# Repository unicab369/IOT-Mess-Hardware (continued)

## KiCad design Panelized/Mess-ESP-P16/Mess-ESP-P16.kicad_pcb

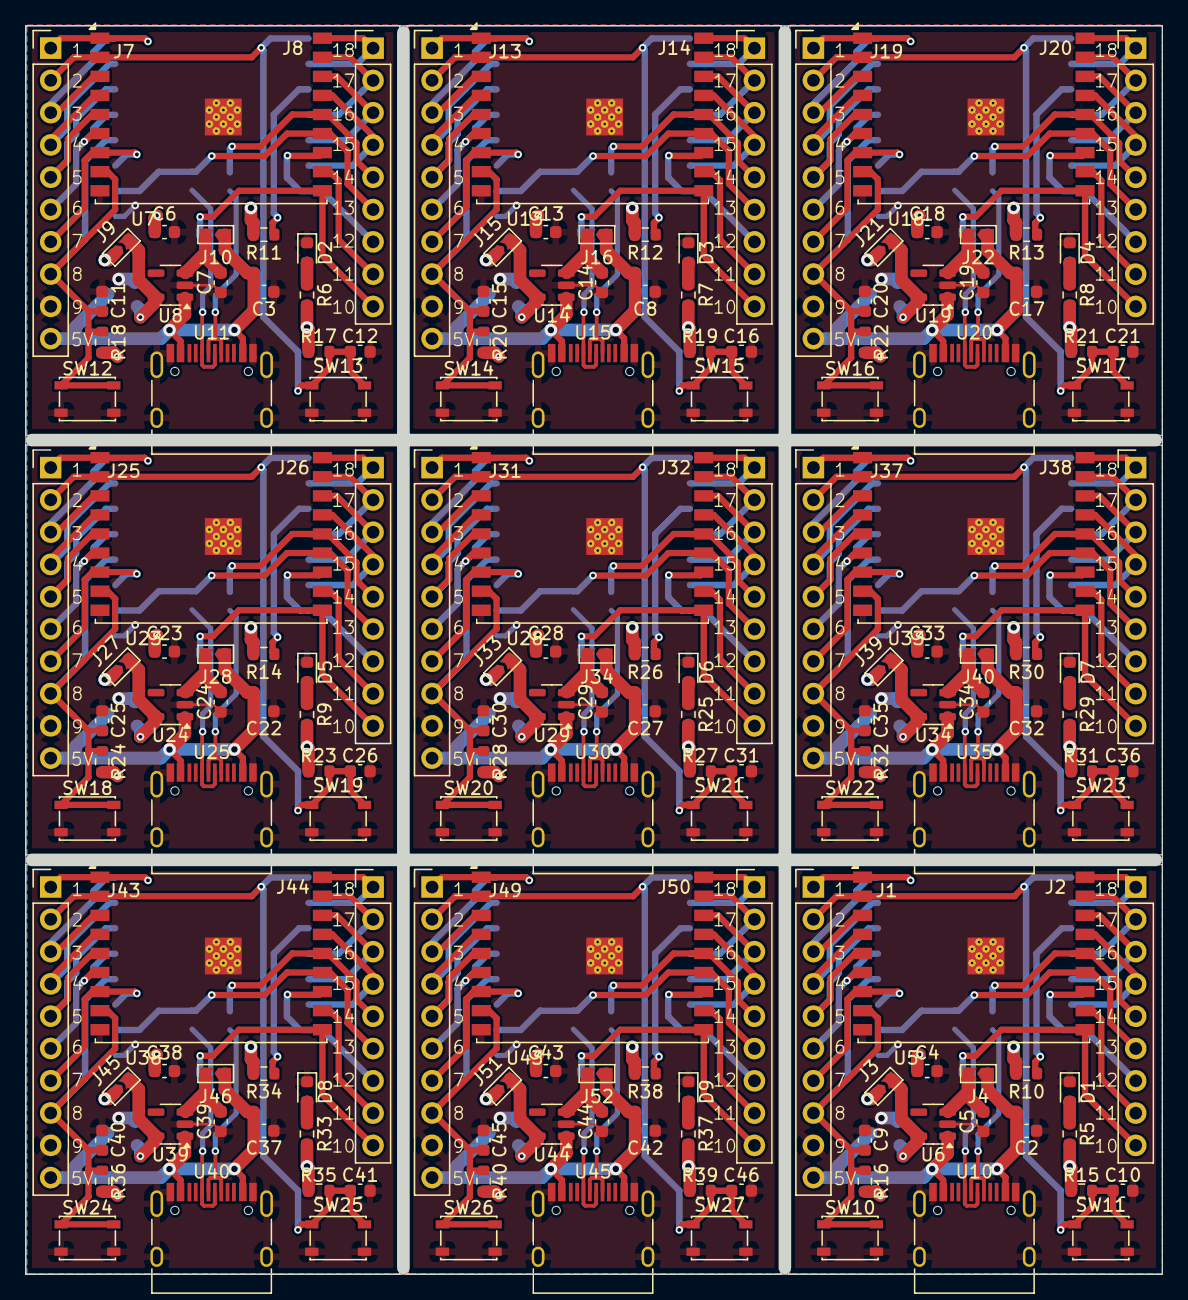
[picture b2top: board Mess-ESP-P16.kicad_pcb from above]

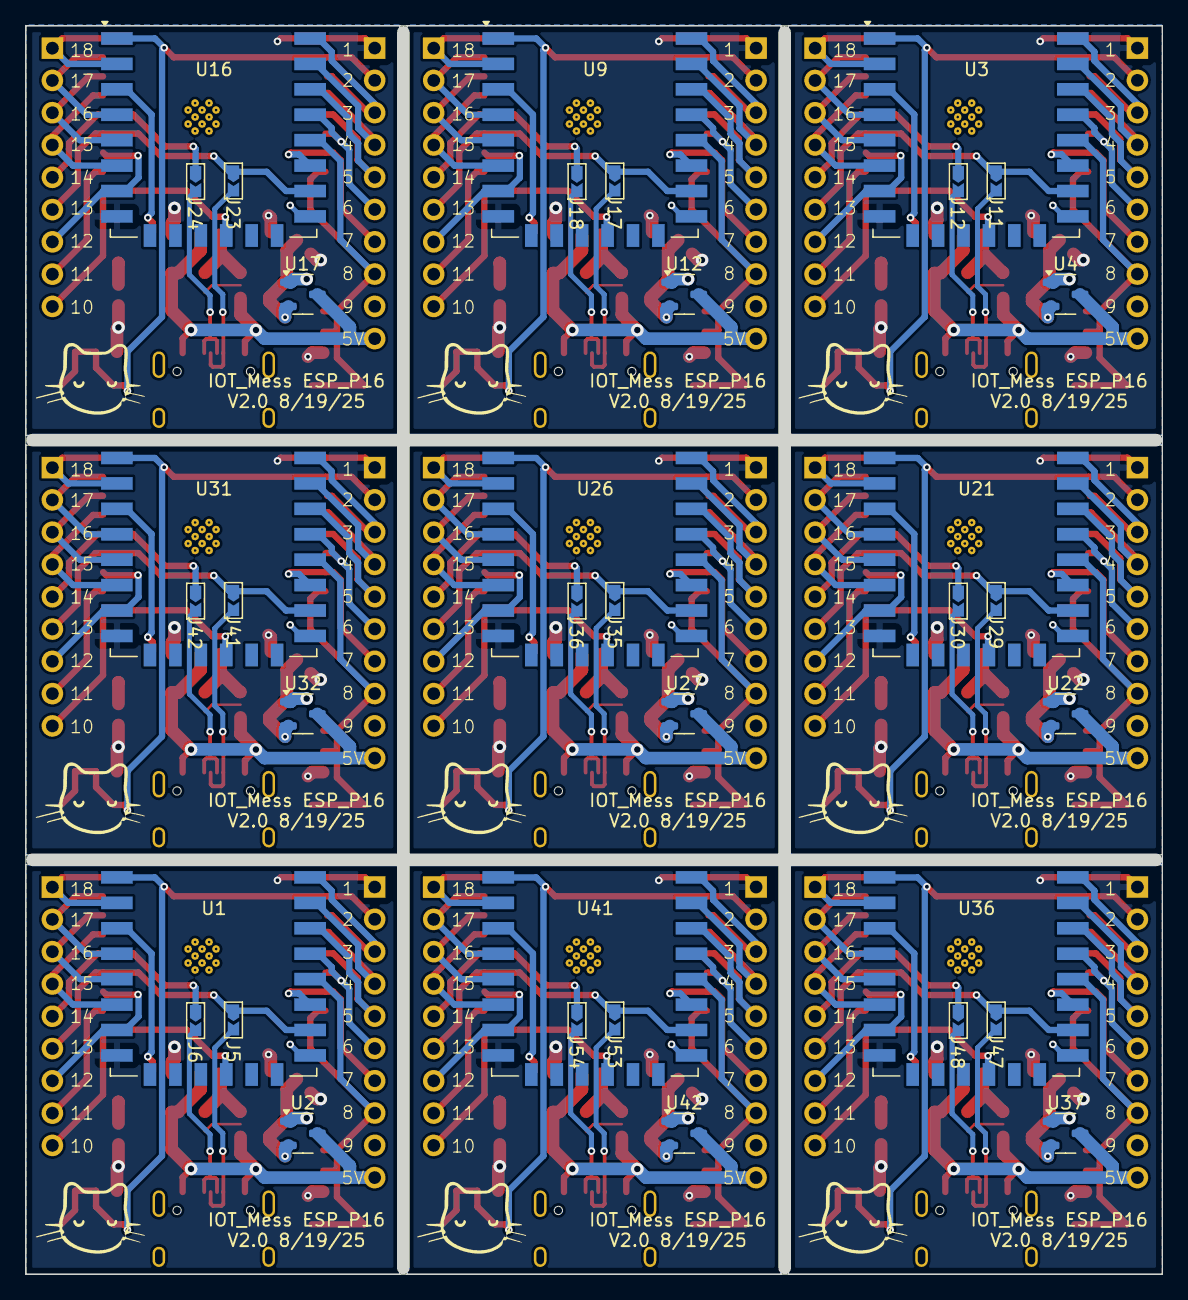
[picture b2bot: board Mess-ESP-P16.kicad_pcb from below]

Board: 2 copper layers, 89.4 x 98.2 mm, 207 parts (36 on the bottom side), 25 nets.

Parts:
C2, C3, C8, C17, C22, C27, C32, C37, C42: 10u; C_0603_1608Metric
C4, C5, C6, C7, C13, C14, C18, C19, C23, C24, C28, C29, C33, C34, C38, C39, C43, C44: 1u; C_0603_1608Metric
C9, C10, C11, C12, C15, C16, C20, C21, C25, C26, C30, C31, C35, C36, C40, C41, C45, C46: .1u; C_0603_1608Metric
D1, D2, D3, D4, D5, D6, D7, D8, D9: LED; LED_0603_1608Metric
J1, J7, J13, J19, J25, J31, J37, J43, J49: Conn_01x10_Pin; PinHeader_1x10_P2.54mm_Vertical
J2, J8, J14, J20, J26, J32, J38, J44, J50: Conn_01x09_Pin; PinHeader_1x09_P2.54mm_Vertical
J3, J4, J5, J6, J9, J10, J11, J12, J15, J16, J17, J18, J21, J22, J23, J24, J27, J28, J29, J30, J33, J34, J35, J36, J39, J40, J41, J42, J45, J46, J47, J48, J51, J52, J53, J54: Jumper_2; Jumpper-triangle
R5, R6, R7, R8, R9, R25, R29, R33, R37: R; R_0603_1608Metric
R10, R11, R12, R13, R14, R15, R16, R17, R18, R19, R20, R21, R22, R23, R24, R26, R27, R28, R30, R31, R32, R34, R35, R36, R38, R39, R40: 10K; R_0603_1608Metric
SW10, SW11, SW12, SW13, SW14, SW15, SW16, SW17, SW18, SW19, SW20, SW21, SW22, SW23, SW24, SW25, SW26, SW27: SW_Push; SW_SPST_PTS810
U1, U3, U9, U16, U21, U26, U31, U36, U41: ESP-12F; ESP-12E
U2, U4, U12, U17, U22, U27, U32, U37, U42: XC6206PxxxMR; SOT-23-3
U5, U7, U13, U18, U23, U28, U33, U38, U43: ESP32-C3-WROOM-02
U6, U8, U14, U19, U24, U29, U34, U39, U44: ME6211C33M5; SOT-23-5
U10, U11, U15, U20, U25, U30, U35, U40, U45: USB_C_Receptacle_USB2.0_16P; USB_C_Receptacle_HRO_TYPE-C-31-M-12

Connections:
5V: C2.1, C3.1, C8.1, C17.1, C22.1, C27.1, C32.1, C37.1, C42.1, J1.10, J4.1 (A), J7.10, J10.1 (A), J13.10, J16.1 (A), J19.10, J22.1 (A), J25.10, J28.1 (A), J31.10, J34.1 (A), J37.10, J40.1 (A), J43.10, J46.1 (A), J49.10, J52.1 (A), U2.3 (VI), U4.3 (VI), U6.1 (V_{IN}), U8.1 (V_{IN}), U10.A4 (VBUS), U10.A9 (VBUS), U10.B4 (VBUS), U10.B9 (VBUS), U11.A4 (VBUS), U11.A9 (VBUS), U11.B4 (VBUS), U11.B9 (VBUS), U12.3 (VI), U14.1 (V_{IN}), U15.A4 (VBUS), U15.A9 (VBUS), U15.B4 (VBUS), U15.B9 (VBUS), U17.3 (VI), U19.1 (V_{IN}), U20.A4 (VBUS), U20.A9 (VBUS), U20.B4 (VBUS), U20.B9 (VBUS), U22.3 (VI), U24.1 (V_{IN}), U25.A4 (VBUS), U25.A9 (VBUS), U25.B4 (VBUS), U25.B9 (VBUS), U27.3 (VI), U29.1 (V_{IN}), U30.A4 (VBUS), U30.A9 (VBUS), U30.B4 (VBUS), U30.B9 (VBUS), U32.3 (VI), U34.1 (V_{IN}), U35.A4 (VBUS), U35.A9 (VBUS), U35.B4 (VBUS), U35.B9 (VBUS), U37.3 (VI), U39.1 (V_{IN}), U40.A4 (VBUS), U40.A9 (VBUS), U40.B4 (VBUS), U40.B9 (VBUS), U42.3 (VI), U44.1 (V_{IN}), U45.A4 (VBUS), U45.A9 (VBUS), U45.B4 (VBUS), U45.B9 (VBUS)
BOOT: C9.1, C11.1, C15.1, C20.1, C25.1, C30.1, C35.1, C40.1, C45.1, J1.8, J7.8, J13.8, J19.8, J25.8, J31.8, J37.8, J43.8, J49.8, R16.1, R18.1, R20.1, R22.1, R24.1, R28.1, R32.1, R36.1, R40.1, SW10.1, SW12.1, SW14.1, SW16.1, SW18.1, SW20.1, SW22.1, SW24.1, SW26.1, U1.18 (GPIO0), U3.18 (GPIO0), U5.8 (GPIO9), U7.8 (GPIO9), U9.18 (GPIO0), U13.8 (GPIO9), U16.18 (GPIO0), U18.8 (GPIO9), U21.18 (GPIO0), U23.8 (GPIO9), U26.18 (GPIO0), U28.8 (GPIO9), U31.18 (GPIO0), U33.8 (GPIO9), U36.18 (GPIO0), U38.8 (GPIO9), U41.18 (GPIO0), U43.8 (GPIO9)
D+: J6.2 (B), J12.2 (B), J18.2 (B), J24.2 (B), J30.2 (B), J36.2 (B), J42.2 (B), J48.2 (B), J54.2 (B), U10.A6 (D+), U10.B6 (D+), U11.A6 (D+), U11.B6 (D+), U15.A6 (D+), U15.B6 (D+), U20.A6 (D+), U20.B6 (D+), U25.A6 (D+), U25.B6 (D+), U30.A6 (D+), U30.B6 (D+), U35.A6 (D+), U35.B6 (D+), U40.A6 (D+), U40.B6 (D+), U45.A6 (D+), U45.B6 (D+)
D-: J5.2 (B), J11.2 (B), J17.2 (B), J23.2 (B), J29.2 (B), J35.2 (B), J41.2 (B), J47.2 (B), J53.2 (B), U10.A7 (D-), U10.B7 (D-), U11.A7 (D-), U11.B7 (D-), U15.A7 (D-), U15.B7 (D-), U20.A7 (D-), U20.B7 (D-), U25.A7 (D-), U25.B7 (D-), U30.A7 (D-), U30.B7 (D-), U35.A7 (D-), U35.B7 (D-), U40.A7 (D-), U40.B7 (D-), U45.A7 (D-), U45.B7 (D-)
unnamed: D1.2 (A), D2.2 (A), D3.2 (A), D4.2 (A), D5.2 (A), D6.2 (A), D7.2 (A), D8.2 (A), D9.2 (A), R5.2, R6.2, R7.2, R8.2, R9.2, R25.2, R29.2, R33.2, R37.2
unnamed: J3.2 (B), J9.2 (B), J15.2 (B), J21.2 (B), J27.2 (B), J33.2 (B), J39.2 (B), J45.2 (B), J51.2 (B), U2.2 (VO), U4.2 (VO), U6.5 (V_{OUT}), U8.5 (V_{OUT}), U12.2 (VO), U14.5 (V_{OUT}), U17.2 (VO), U19.5 (V_{OUT}), U22.2 (VO), U24.5 (V_{OUT}), U27.2 (VO), U29.5 (V_{OUT}), U32.2 (VO), U34.5 (V_{OUT}), U37.2 (VO), U39.5 (V_{OUT}), U42.2 (VO), U44.5 (V_{OUT})
unnamed: C5.1, C7.1, C14.1, C19.1, C24.1, C29.1, C34.1, C39.1, C44.1, J4.2 (B), J10.2 (B), J16.2 (B), J22.2 (B), J28.2 (B), J34.2 (B), J40.2 (B), J46.2 (B), J52.2 (B), U6.3 (CE), U8.3 (CE), U14.3 (CE), U19.3 (CE), U24.3 (CE), U29.3 (CE), U34.3 (CE), U39.3 (CE), U44.3 (CE)
unnamed: R10.1, R11.1, R12.1, R13.1, R14.1, R26.1, R30.1, R34.1, R38.1, U1.3 (EN), U3.3 (EN), U9.3 (EN), U16.3 (EN), U21.3 (EN), U26.3 (EN), U31.3 (EN), U36.3 (EN), U41.3 (EN)
P1: C4.1, C6.1, C13.1, C18.1, C23.1, C28.1, C33.1, C38.1, C43.1, J1.1, J3.1 (A), J7.1, J9.1 (A), J13.1, J15.1 (A), J19.1, J21.1 (A), J25.1, J27.1 (A), J31.1, J33.1 (A), J37.1, J39.1 (A), J43.1, J45.1 (A), J49.1, J51.1 (A), R5.1, R6.1, R7.1, R8.1, R9.1, R10.2, R11.2, R12.2, R13.2, R14.2, R15.2, R16.2, R17.2, R18.2, R19.2, R20.2, R21.2, R22.2, R23.2, R24.2, R25.1, R26.2, R27.2, R28.2, R29.1, R30.2, R31.2, R32.2, R33.1, R34.2, R35.2, R36.2, R37.1, R38.2, R39.2, R40.2, U1.8 (VCC), U3.8 (VCC), U5.1 (3V3), U7.1 (3V3), U9.8 (VCC), U13.1 (3V3), U16.8 (VCC), U18.1 (3V3), U21.8 (VCC), U23.1 (3V3), U26.8 (VCC), U28.1 (3V3), U31.8 (VCC), U33.1 (3V3), U36.8 (VCC), U38.1 (3V3), U41.8 (VCC), U43.1 (3V3)
P2: C10.1, C12.1, C16.1, C21.1, C26.1, C31.1, C36.1, C41.1, C46.1, J1.2, J7.2, J13.2, J19.2, J25.2, J31.2, J37.2, J43.2, J49.2, R15.1, R17.1, R19.1, R21.1, R23.1, R27.1, R31.1, R35.1, R39.1, SW11.1, SW13.1, SW15.1, SW17.1, SW19.1, SW21.1, SW23.1, SW25.1, SW27.1, U1.1 (~RST), U3.1 (~RST), U5.2 (EN/CHIP_PU), U7.2 (EN/CHIP_PU), U9.1 (~RST), U13.2 (EN/CHIP_PU), U16.1 (~RST), U18.2 (EN/CHIP_PU), U21.1 (~RST), U23.2 (EN/CHIP_PU), U26.1 (~RST), U28.2 (EN/CHIP_PU), U31.1 (~RST), U33.2 (EN/CHIP_PU), U36.1 (~RST), U38.2 (EN/CHIP_PU), U41.1 (~RST), U43.2 (EN/CHIP_PU)
P3: J1.3, J7.3, J13.3, J19.3, J25.3, J31.3, J37.3, J43.3, J49.3, U1.22 (GPIO1/TXD), U3.22 (GPIO1/TXD), U5.3 (GPIO4/ADC1_CH4), U7.3 (GPIO4/ADC1_CH4), U9.22 (GPIO1/TXD), U13.3 (GPIO4/ADC1_CH4), U16.22 (GPIO1/TXD), U18.3 (GPIO4/ADC1_CH4), U21.22 (GPIO1/TXD), U23.3 (GPIO4/ADC1_CH4), U26.22 (GPIO1/TXD), U28.3 (GPIO4/ADC1_CH4), U31.22 (GPIO1/TXD), U33.3 (GPIO4/ADC1_CH4), U36.22 (GPIO1/TXD), U38.3 (GPIO4/ADC1_CH4), U41.22 (GPIO1/TXD), U43.3 (GPIO4/ADC1_CH4)
P4: J1.4, J7.4, J13.4, J19.4, J25.4, J31.4, J37.4, J43.4, J49.4, U1.21 (GPIO3/RXD), U3.21 (GPIO3/RXD), U5.4 (GPIO5/ADC2_CH0), U7.4 (GPIO5/ADC2_CH0), U9.21 (GPIO3/RXD), U13.4 (GPIO5/ADC2_CH0), U16.21 (GPIO3/RXD), U18.4 (GPIO5/ADC2_CH0), U21.21 (GPIO3/RXD), U23.4 (GPIO5/ADC2_CH0), U26.21 (GPIO3/RXD), U28.4 (GPIO5/ADC2_CH0), U31.21 (GPIO3/RXD), U33.4 (GPIO5/ADC2_CH0), U36.21 (GPIO3/RXD), U38.4 (GPIO5/ADC2_CH0), U41.21 (GPIO3/RXD), U43.4 (GPIO5/ADC2_CH0)
P5: J1.5, J7.5, J13.5, J19.5, J25.5, J31.5, J37.5, J43.5, J49.5, U1.20 (GPIO5), U3.20 (GPIO5), U5.5 (GPIO6), U7.5 (GPIO6), U9.20 (GPIO5), U13.5 (GPIO6), U16.20 (GPIO5), U18.5 (GPIO6), U21.20 (GPIO5), U23.5 (GPIO6), U26.20 (GPIO5), U28.5 (GPIO6), U31.20 (GPIO5), U33.5 (GPIO6), U36.20 (GPIO5), U38.5 (GPIO6), U41.20 (GPIO5), U43.5 (GPIO6)
P6: J1.6, J7.6, J13.6, J19.6, J25.6, J31.6, J37.6, J43.6, J49.6, U1.19 (GPIO4), U3.19 (GPIO4), U5.6 (GPIO7), U7.6 (GPIO7), U9.19 (GPIO4), U13.6 (GPIO7), U16.19 (GPIO4), U18.6 (GPIO7), U21.19 (GPIO4), U23.6 (GPIO7), U26.19 (GPIO4), U28.6 (GPIO7), U31.19 (GPIO4), U33.6 (GPIO7), U36.19 (GPIO4), U38.6 (GPIO7), U41.19 (GPIO4), U43.6 (GPIO7)
P7: J1.7, J7.7, J13.7, J19.7, J25.7, J31.7, J37.7, J43.7, J49.7, U1.17 (GPIO2), U3.17 (GPIO2), U5.7 (GPIO8), U7.7 (GPIO8), U9.17 (GPIO2), U13.7 (GPIO8), U16.17 (GPIO2), U18.7 (GPIO8), U21.17 (GPIO2), U23.7 (GPIO8), U26.17 (GPIO2), U28.7 (GPIO8), U31.17 (GPIO2), U33.7 (GPIO8), U36.17 (GPIO2), U38.7 (GPIO8), U41.17 (GPIO2), U43.7 (GPIO8)
P9: C2.2, C3.2, C4.2, C5.2, C6.2, C7.2, C8.2, C9.2, C10.2, C11.2, C12.2, C13.2, C14.2, C15.2, C16.2, C17.2, C18.2, C19.2, C20.2, C21.2, C22.2, C23.2, C24.2, C25.2, C26.2, C27.2, C28.2, C29.2, C30.2, C31.2, C32.2, C33.2, C34.2, C35.2, C36.2, C37.2, C38.2, C39.2, C40.2, C41.2, C42.2, C43.2, C44.2, C45.2, C46.2, D1.1 (K), D2.1 (K), D3.1 (K), D4.1 (K), D5.1 (K), D6.1 (K), D7.1 (K), D8.1 (K), D9.1 (K), J1.9, J7.9, J13.9, J19.9, J25.9, J31.9, J37.9, J43.9, J49.9, SW10.2, SW11.2, SW12.2, SW13.2, SW14.2, SW15.2, SW16.2, SW17.2, SW18.2, SW19.2, SW20.2, SW21.2, SW22.2, SW23.2, SW24.2, SW25.2, SW26.2, SW27.2, U1.15 (GND), U2.1 (GND), U3.15 (GND), U4.1 (GND), U5.9 (GND), U5.19 (GND), U6.2 (V_{SS}), U7.9 (GND), U7.19 (GND), U8.2 (V_{SS}), U9.15 (GND), U10.A1 (GND), U10.A12 (GND), U10.B1 (GND), U10.B12 (GND), U10.S1 (SHIELD), U11.A1 (GND), U11.A12 (GND), U11.B1 (GND), U11.B12 (GND), U11.S1 (SHIELD), U12.1 (GND), U13.9 (GND), U13.19 (GND), U14.2 (V_{SS}), U15.A1 (GND), U15.A12 (GND), U15.B1 (GND), U15.B12 (GND), U15.S1 (SHIELD), U16.15 (GND), U17.1 (GND), U18.9 (GND), U18.19 (GND), U19.2 (V_{SS}), U20.A1 (GND), U20.A12 (GND), U20.B1 (GND), U20.B12 (GND), U20.S1 (SHIELD), U21.15 (GND), U22.1 (GND), U23.9 (GND), U23.19 (GND), U24.2 (V_{SS}), U25.A1 (GND), U25.A12 (GND), U25.B1 (GND), U25.B12 (GND), U25.S1 (SHIELD), U26.15 (GND), U27.1 (GND), U28.9 (GND), U28.19 (GND), U29.2 (V_{SS}), U30.A1 (GND), U30.A12 (GND), U30.B1 (GND), U30.B12 (GND), U30.S1 (SHIELD), U31.15 (GND), U32.1 (GND), U33.9 (GND), U33.19 (GND), U34.2 (V_{SS}), U35.A1 (GND), U35.A12 (GND), U35.B1 (GND), U35.B12 (GND), U35.S1 (SHIELD), U36.15 (GND), U37.1 (GND), U38.9 (GND), U38.19 (GND), U39.2 (V_{SS}), U40.A1 (GND), U40.A12 (GND), U40.B1 (GND), U40.B12 (GND), U40.S1 (SHIELD), U41.15 (GND), U42.1 (GND), U43.9 (GND), U43.19 (GND), U44.2 (V_{SS}), U45.A1 (GND), U45.A12 (GND), U45.B1 (GND), U45.B12 (GND), U45.S1 (SHIELD)
P10: J2.9, J8.9, J14.9, J20.9, J26.9, J32.9, J38.9, J44.9, J50.9, U1.12 (GPIO10), U3.12 (GPIO10), U5.10 (GPIO10), U7.10 (GPIO10), U9.12 (GPIO10), U13.10 (GPIO10), U16.12 (GPIO10), U18.10 (GPIO10), U21.12 (GPIO10), U23.10 (GPIO10), U26.12 (GPIO10), U28.10 (GPIO10), U31.12 (GPIO10), U33.10 (GPIO10), U36.12 (GPIO10), U38.10 (GPIO10), U41.12 (GPIO10), U43.10 (GPIO10)
P11: J2.8, J8.8, J14.8, J20.8, J26.8, J32.8, J38.8, J44.8, J50.8, U5.11 (GPIO20/U0RXD), U7.11 (GPIO20/U0RXD), U13.11 (GPIO20/U0RXD), U18.11 (GPIO20/U0RXD), U23.11 (GPIO20/U0RXD), U28.11 (GPIO20/U0RXD), U33.11 (GPIO20/U0RXD), U38.11 (GPIO20/U0RXD), U43.11 (GPIO20/U0RXD)
P12: J2.7, J8.7, J14.7, J20.7, J26.7, J32.7, J38.7, J44.7, J50.7, U1.7 (GPIO13), U3.7 (GPIO13), U5.12 (GPIO21/U0TXD), U7.12 (GPIO21/U0TXD), U9.7 (GPIO13), U13.12 (GPIO21/U0TXD), U16.7 (GPIO13), U18.12 (GPIO21/U0TXD), U21.7 (GPIO13), U23.12 (GPIO21/U0TXD), U26.7 (GPIO13), U28.12 (GPIO21/U0TXD), U31.7 (GPIO13), U33.12 (GPIO21/U0TXD), U36.7 (GPIO13), U38.12 (GPIO21/U0TXD), U41.7 (GPIO13), U43.12 (GPIO21/U0TXD)
P13: J2.6, J5.1 (A), J8.6, J11.1 (A), J14.6, J17.1 (A), J20.6, J23.1 (A), J26.6, J29.1 (A), J32.6, J35.1 (A), J38.6, J41.1 (A), J44.6, J47.1 (A), J50.6, J53.1 (A), U1.16 (GPIO15), U3.16 (GPIO15), U5.13 (GPIO18/USB_D-), U7.13 (GPIO18/USB_D-), U9.16 (GPIO15), U13.13 (GPIO18/USB_D-), U16.16 (GPIO15), U18.13 (GPIO18/USB_D-), U21.16 (GPIO15), U23.13 (GPIO18/USB_D-), U26.16 (GPIO15), U28.13 (GPIO18/USB_D-), U31.16 (GPIO15), U33.13 (GPIO18/USB_D-), U36.16 (GPIO15), U38.13 (GPIO18/USB_D-), U41.16 (GPIO15), U43.13 (GPIO18/USB_D-)
P14: J2.5, J6.1 (A), J8.5, J12.1 (A), J14.5, J18.1 (A), J20.5, J24.1 (A), J26.5, J30.1 (A), J32.5, J36.1 (A), J38.5, J42.1 (A), J44.5, J48.1 (A), J50.5, J54.1 (A), U5.14 (GPIO19/USB_D+), U7.14 (GPIO19/USB_D+), U13.14 (GPIO19/USB_D+), U18.14 (GPIO19/USB_D+), U23.14 (GPIO19/USB_D+), U28.14 (GPIO19/USB_D+), U33.14 (GPIO19/USB_D+), U38.14 (GPIO19/USB_D+), U43.14 (GPIO19/USB_D+)
P15: J2.4, J8.4, J14.4, J20.4, J26.4, J32.4, J38.4, J44.4, J50.4, U1.6 (GPIO12), U3.6 (GPIO12), U5.15 (GPIO3/ADC1_CH3), U7.15 (GPIO3/ADC1_CH3), U9.6 (GPIO12), U13.15 (GPIO3/ADC1_CH3), U16.6 (GPIO12), U18.15 (GPIO3/ADC1_CH3), U21.6 (GPIO12), U23.15 (GPIO3/ADC1_CH3), U26.6 (GPIO12), U28.15 (GPIO3/ADC1_CH3), U31.6 (GPIO12), U33.15 (GPIO3/ADC1_CH3), U36.6 (GPIO12), U38.15 (GPIO3/ADC1_CH3), U41.6 (GPIO12), U43.15 (GPIO3/ADC1_CH3)
P16: J2.3, J8.3, J14.3, J20.3, J26.3, J32.3, J38.3, J44.3, J50.3, U1.5 (GPIO14), U3.5 (GPIO14), U5.16 (GPIO2/ADC1_CH2), U7.16 (GPIO2/ADC1_CH2), U9.5 (GPIO14), U13.16 (GPIO2/ADC1_CH2), U16.5 (GPIO14), U18.16 (GPIO2/ADC1_CH2), U21.5 (GPIO14), U23.16 (GPIO2/ADC1_CH2), U26.5 (GPIO14), U28.16 (GPIO2/ADC1_CH2), U31.5 (GPIO14), U33.16 (GPIO2/ADC1_CH2), U36.5 (GPIO14), U38.16 (GPIO2/ADC1_CH2), U41.5 (GPIO14), U43.16 (GPIO2/ADC1_CH2)
P17: J2.2, J8.2, J14.2, J20.2, J26.2, J32.2, J38.2, J44.2, J50.2, U1.4 (GPIO16), U3.4 (GPIO16), U5.17 (GPIO1/ADC1_CH1/XTAL_32K_N), U7.17 (GPIO1/ADC1_CH1/XTAL_32K_N), U9.4 (GPIO16), U13.17 (GPIO1/ADC1_CH1/XTAL_32K_N), U16.4 (GPIO16), U18.17 (GPIO1/ADC1_CH1/XTAL_32K_N), U21.4 (GPIO16), U23.17 (GPIO1/ADC1_CH1/XTAL_32K_N), U26.4 (GPIO16), U28.17 (GPIO1/ADC1_CH1/XTAL_32K_N), U31.4 (GPIO16), U33.17 (GPIO1/ADC1_CH1/XTAL_32K_N), U36.4 (GPIO16), U38.17 (GPIO1/ADC1_CH1/XTAL_32K_N), U41.4 (GPIO16), U43.17 (GPIO1/ADC1_CH1/XTAL_32K_N)
P18: J2.1, J8.1, J14.1, J20.1, J26.1, J32.1, J38.1, J44.1, J50.1, U1.2 (ADC), U3.2 (ADC), U5.18 (GPIO0/ADC1_CH0/XTAL_32K_P), U7.18 (GPIO0/ADC1_CH0/XTAL_32K_P), U9.2 (ADC), U13.18 (GPIO0/ADC1_CH0/XTAL_32K_P), U16.2 (ADC), U18.18 (GPIO0/ADC1_CH0/XTAL_32K_P), U21.2 (ADC), U23.18 (GPIO0/ADC1_CH0/XTAL_32K_P), U26.2 (ADC), U28.18 (GPIO0/ADC1_CH0/XTAL_32K_P), U31.2 (ADC), U33.18 (GPIO0/ADC1_CH0/XTAL_32K_P), U36.2 (ADC), U38.18 (GPIO0/ADC1_CH0/XTAL_32K_P), U41.2 (ADC), U43.18 (GPIO0/ADC1_CH0/XTAL_32K_P)
